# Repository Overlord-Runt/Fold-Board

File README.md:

# Fold Board
Made By Overlord Runt // Taran The Idiot

## The Fold Board
Its the second keyboard in my line of Taranium boards. It is a keyboard that folds! It has 66 Keys and an OLED for funny stuff.

If you like this project, please give it a star!

YouTube vid: https://youtube.com/shorts/LQNGhtRMvZQ?si=ZyAIBXtM6X78Itwt

## CAD

Here is a full [CAD Build](https://cad.onshape.com/documents/464e86edd9a4b3695068071c/w/4e80d06eb9a86776c724470c/e/258c53a4e91dc0ec03e526f0) of the keyboard.\
It uses a rubber band to hold the 2 halves together and I am probably gonna have to work on the joint a bit when i get the parts.

The case is 44cm tall when layed flat out which is pretty good for a folding board. I made sure to keep the joint loose but strong enough to stay on so it doesnt wear down as muhttps://youtube.com/shorts/LQNGhtRMvZQ?si=ZyAIBXtM6X78Itwtch and stays nice. I suggest printing it from petg so you can get more slip.

Here are some shots of what it looks like open and folded.

I spent majority of my time here going through different renditions of the bridge and trying different ways to make the fold work while keeping it as a keyboard that it viable to use.

## PCB

The pcb was done pretty quickly and I only did about 1 revision while making it.\
The pcb folder contains the original design files while right and left side have the files with the respective side isolated for fabrication purposes. gerbers can also be found in those folders.

I used 16 jumper wires to bridge the connections of one half to the other instead of going for the traditional approach with trrs. I think will add a nice look to it, especially across the bridge.

My schematic is pretty normal. Average split board stuff.

## Firmware

This keyboard uses QMK firmware that can be found in the firmware folder. Unfortunately it isnt compiled as my computer is too old to install the QMK command line but I will update it as soon as I can. For now you need to install the command line yourself [here](https://docs.qmk.fm/newbs_getting_started).

This was probably my fastest firmware built ever. Its all thanks to github copilot. It completely gets rid of all the zombie work. I can finally be free. There is no greater blessing to the world.

## BOM
BOM can be found [here](https://github.com/Overlord-Runt/Fold-Board/blob/main/BOM.md) but here is a general list:
- 66 MX Switches
- 66 diodes
- 2 2U stablisers
- 64 1U keycaps
- 2 2U keycaps
- 2 PCBs
- 5 3D printd Case parts
- SSD1306 128x32 OLED
- 16 50mm long wires
- 1 Orpheus Pico(or a normal pico if you dont have one)
- 1 large rubber band
- 8 M3D5L6 Heatsets
- 8 M3 30mm long screws

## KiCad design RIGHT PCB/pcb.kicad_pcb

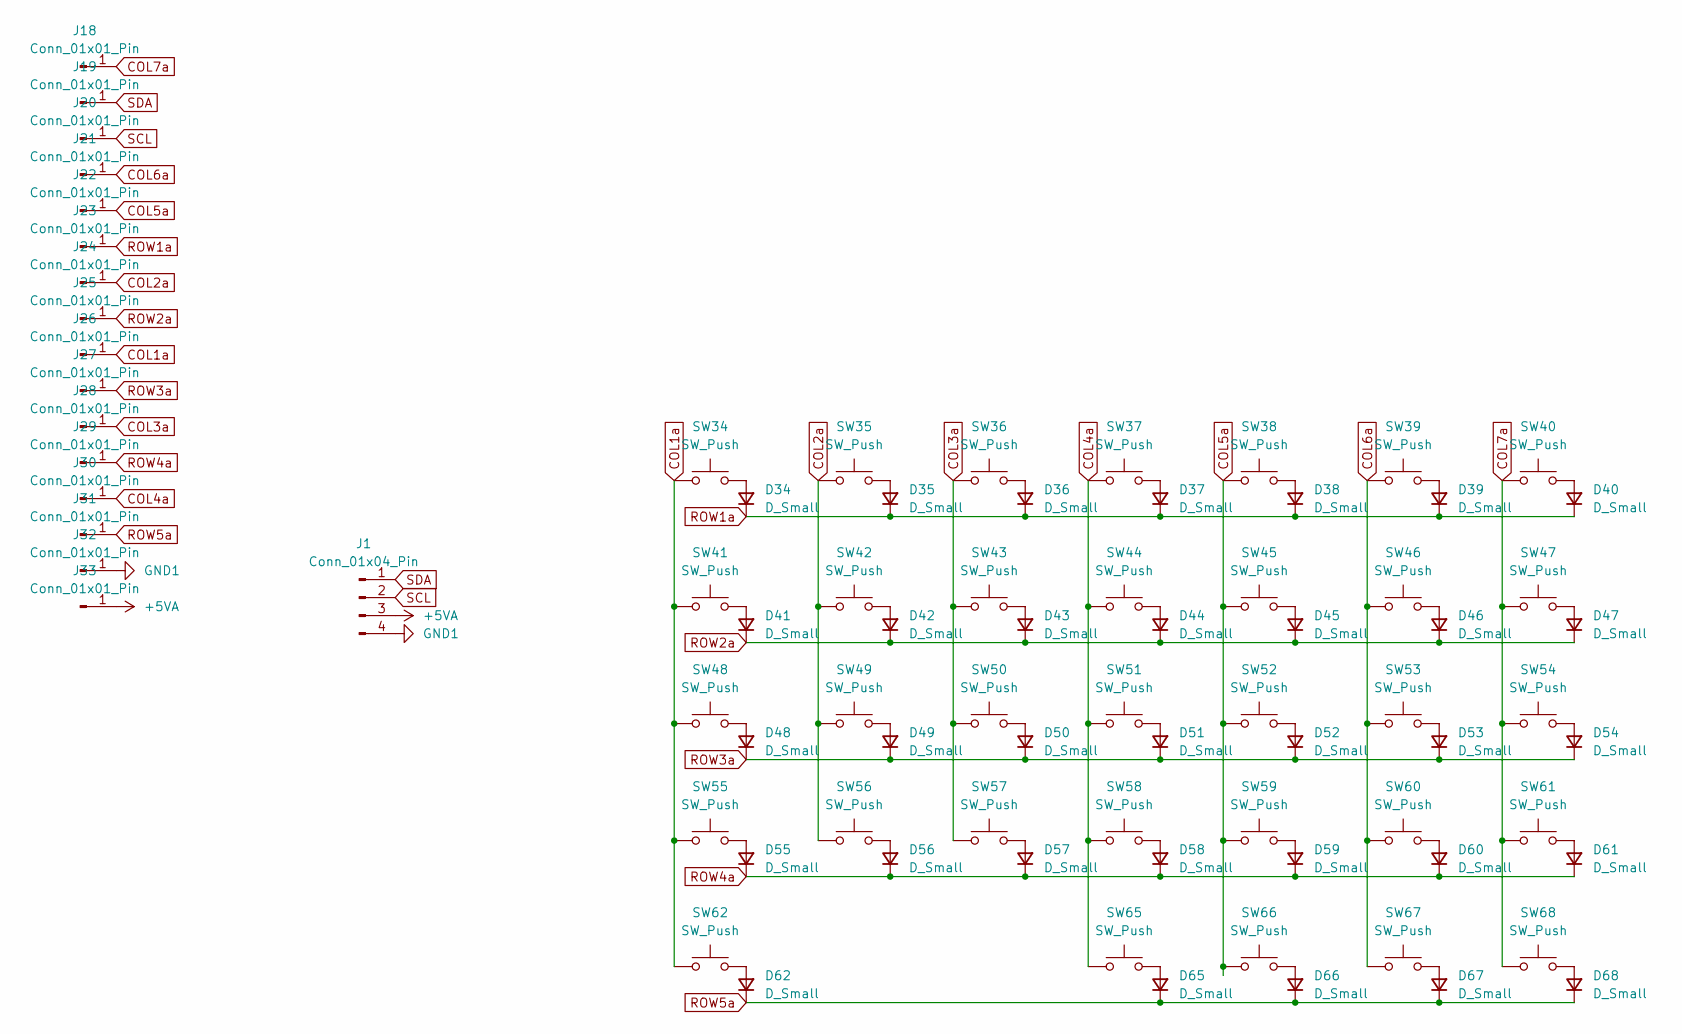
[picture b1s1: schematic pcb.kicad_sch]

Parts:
D34, D35, D36, D37, D38, D39, D40, D41, D42, D43, D44, D45, D46, D47, D48, D49, D50, D51, D52, D53, D54, D55, D56, D57, D58, D59, D60, D61, D62, D65, D66, D67, D68: D_Small; D_DO-35_SOD27_P7.62mm_Horizontal
J1: Conn_01x04_Pin; PinSocket_1x04_P2.54mm_Vertical
J18, J19, J20, J21, J22, J23, J24, J25, J26, J27, J28, J29, J30, J31, J32, J33: Conn_01x01_Pin; TestPoint_Pad_3.0x3.0mm
SW34, SW35, SW36, SW37, SW38, SW39, SW40, SW41, SW42, SW43, SW44, SW45, SW46, SW47, SW48, SW49, SW50, SW51, SW52, SW53, SW54, SW55, SW56, SW57, SW58, SW59, SW60, SW61, SW65, SW66, SW67, SW68: SW_Push; SW_Cherry_MX_1.00u_PCB
SW62: SW_Push; SW_Cherry_MX_2.00u_PCB

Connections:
+5VA: J1.3, J33.1
COL1a: J26.1, SW34.1, SW41.1, SW48.1, SW55.1, SW62.1
COL2a: J24.1, SW35.1, SW42.1, SW49.1, SW56.1
COL3a: J28.1, SW36.1, SW43.1, SW50.1, SW57.1
COL4a: J30.1, SW37.1, SW44.1, SW51.1, SW58.1, SW65.1
COL5a: J22.1, SW38.1, SW45.1, SW52.1, SW59.1, SW66.1
COL6a: J21.1, SW39.1, SW46.1, SW53.1, SW60.1, SW67.1
COL7a: J18.1, SW40.1, SW47.1, SW54.1, SW61.1, SW68.1
GND1: J1.4, J32.1
unnamed: D34.2 (A), SW34.2
unnamed: D35.2 (A), SW35.2
unnamed: D36.2 (A), SW36.2
unnamed: D37.2 (A), SW37.2
unnamed: D38.2 (A), SW38.2
unnamed: D39.2 (A), SW39.2
unnamed: D40.2 (A), SW40.2
unnamed: D41.2 (A), SW41.2
unnamed: D42.2 (A), SW42.2
unnamed: D43.2 (A), SW43.2
unnamed: D44.2 (A), SW44.2
unnamed: D45.2 (A), SW45.2
unnamed: D46.2 (A), SW46.2
unnamed: D47.2 (A), SW47.2
unnamed: D48.2 (A), SW48.2
unnamed: D49.2 (A), SW49.2
unnamed: D50.2 (A), SW50.2
unnamed: D51.2 (A), SW51.2
unnamed: D52.2 (A), SW52.2
unnamed: D53.2 (A), SW53.2
unnamed: D54.2 (A), SW54.2
unnamed: D55.2 (A), SW55.2
unnamed: D56.2 (A), SW56.2
unnamed: D57.2 (A), SW57.2
unnamed: D58.2 (A), SW58.2
unnamed: D59.2 (A), SW59.2
unnamed: D60.2 (A), SW60.2
unnamed: D61.2 (A), SW61.2
unnamed: D62.2 (A), SW62.2
unnamed: D65.2 (A), SW65.2
unnamed: D66.2 (A), SW66.2
unnamed: D67.2 (A), SW67.2
unnamed: D68.2 (A), SW68.2
ROW1a: D34.1 (K), D35.1 (K), D36.1 (K), D37.1 (K), D38.1 (K), D39.1 (K), D40.1 (K), J23.1
ROW2a: D41.1 (K), D42.1 (K), D43.1 (K), D44.1 (K), D45.1 (K), D46.1 (K), D47.1 (K), J25.1
ROW3a: D48.1 (K), D49.1 (K), D50.1 (K), D51.1 (K), D52.1 (K), D53.1 (K), D54.1 (K), J27.1
ROW4a: D55.1 (K), D56.1 (K), D57.1 (K), D58.1 (K), D59.1 (K), D60.1 (K), D61.1 (K), J29.1
ROW5a: D62.1 (K), D65.1 (K), D66.1 (K), D67.1 (K), D68.1 (K), J31.1
SCL: J1.2, J20.1
SDA: J1.1, J19.1

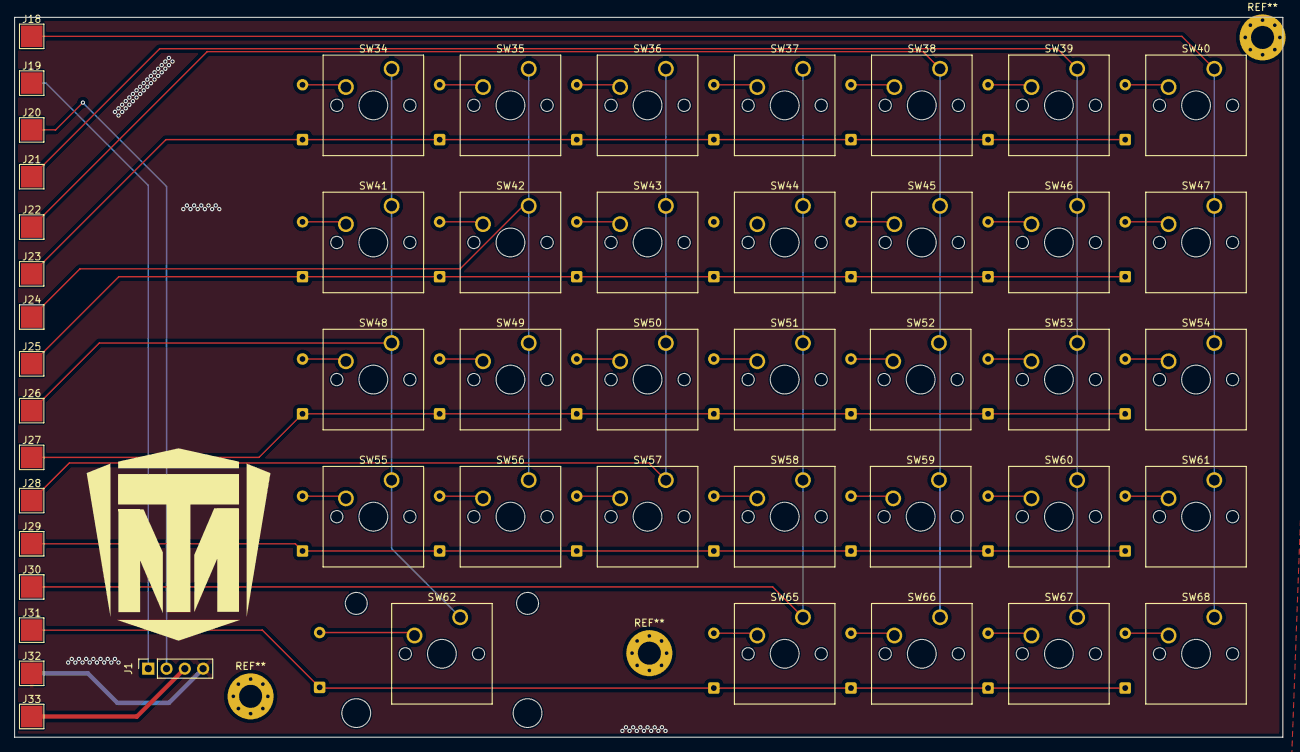
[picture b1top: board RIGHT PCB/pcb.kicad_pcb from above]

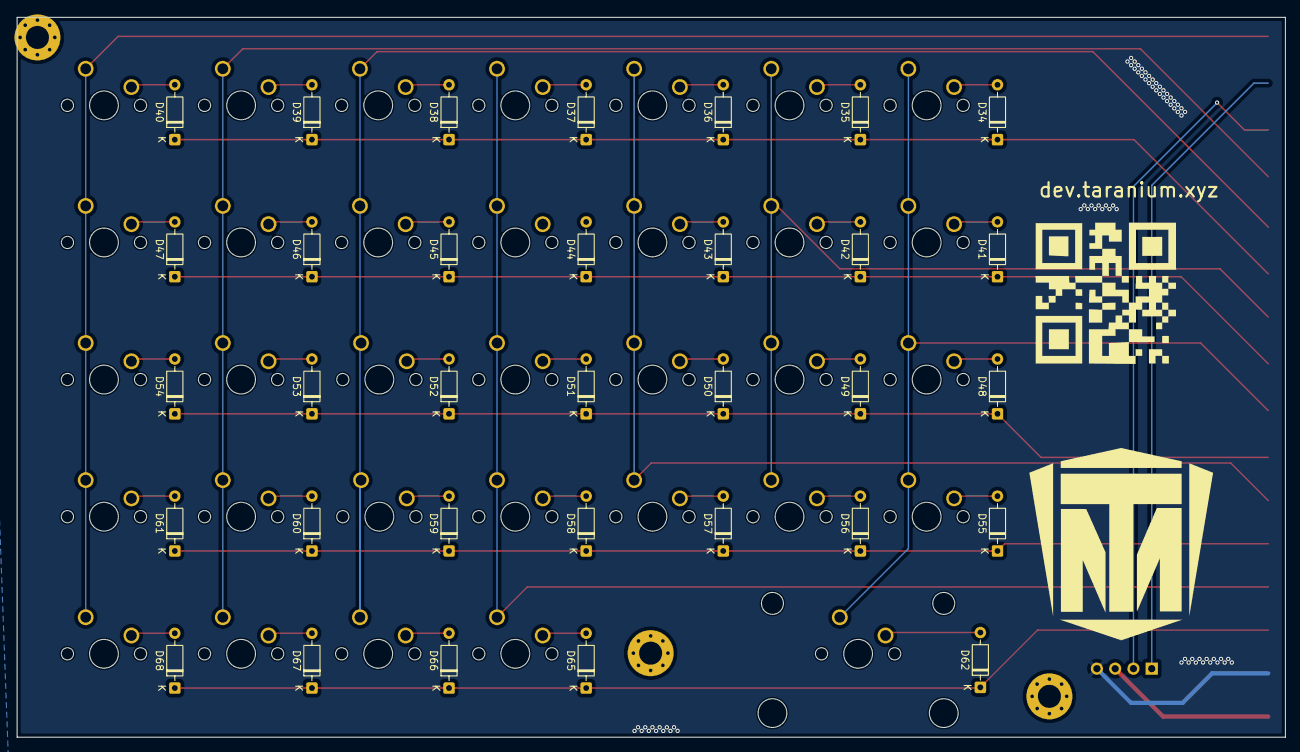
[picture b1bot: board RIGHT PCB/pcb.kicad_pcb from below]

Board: 2 copper layers, 176.2 x 100.0 mm, 83 parts (33 on the bottom side), 49 nets.

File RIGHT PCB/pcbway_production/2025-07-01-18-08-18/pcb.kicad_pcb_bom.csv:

Designator,Quantity,Value,Footprint,Package,MPN,DNP,Mount_Type,Description,Sim.Device,Sim.Pins
"D34, D35, D36, D37, D38, D39, D40, D41, D42, D43, D44, D45, D46, D47, D48, D49, D50, D51, D52, D53, D54, D55, D56, D57, D58, D59, D60, D61, D62, D65, D66, D67, D68",33,D_Small,D_DO-35_SOD27_P7.62mm_Horizontal,,,,tht,"Diode, small symbol",D,1=K 2=A
J1,1,Conn_01x04_Pin,PinSocket_1x04_P2.54mm_Vertical,,,,tht,"Generic connector, single row, 01x04, script generated",,
"J18, J19, J20, J21, J22, J23, J24, J25, J26, J27, J28, J29, J30, J31, J32, J33",16,Conn_01x01_Pin,TestPoint_Pad_3.0x3.0mm,,,,tht,"Generic connector, single row, 01x01, script generated",,
"SW34, SW35, SW36, SW37, SW38, SW39, SW40, SW41, SW42, SW43, SW44, SW45, SW46, SW47, SW48, SW49, SW50, SW51, SW52, SW53, SW54, SW55, SW56, SW57, SW58, SW59, SW60, SW61, SW65, SW66, SW67, SW68",32,SW_Push,SW_Cherry_MX_1.00u_PCB,,,,tht,"Push button switch, generic, two pins",,
SW62,1,SW_Push,SW_Cherry_MX_2.00u_PCB,,,,tht,"Push button switch, generic, two pins",,

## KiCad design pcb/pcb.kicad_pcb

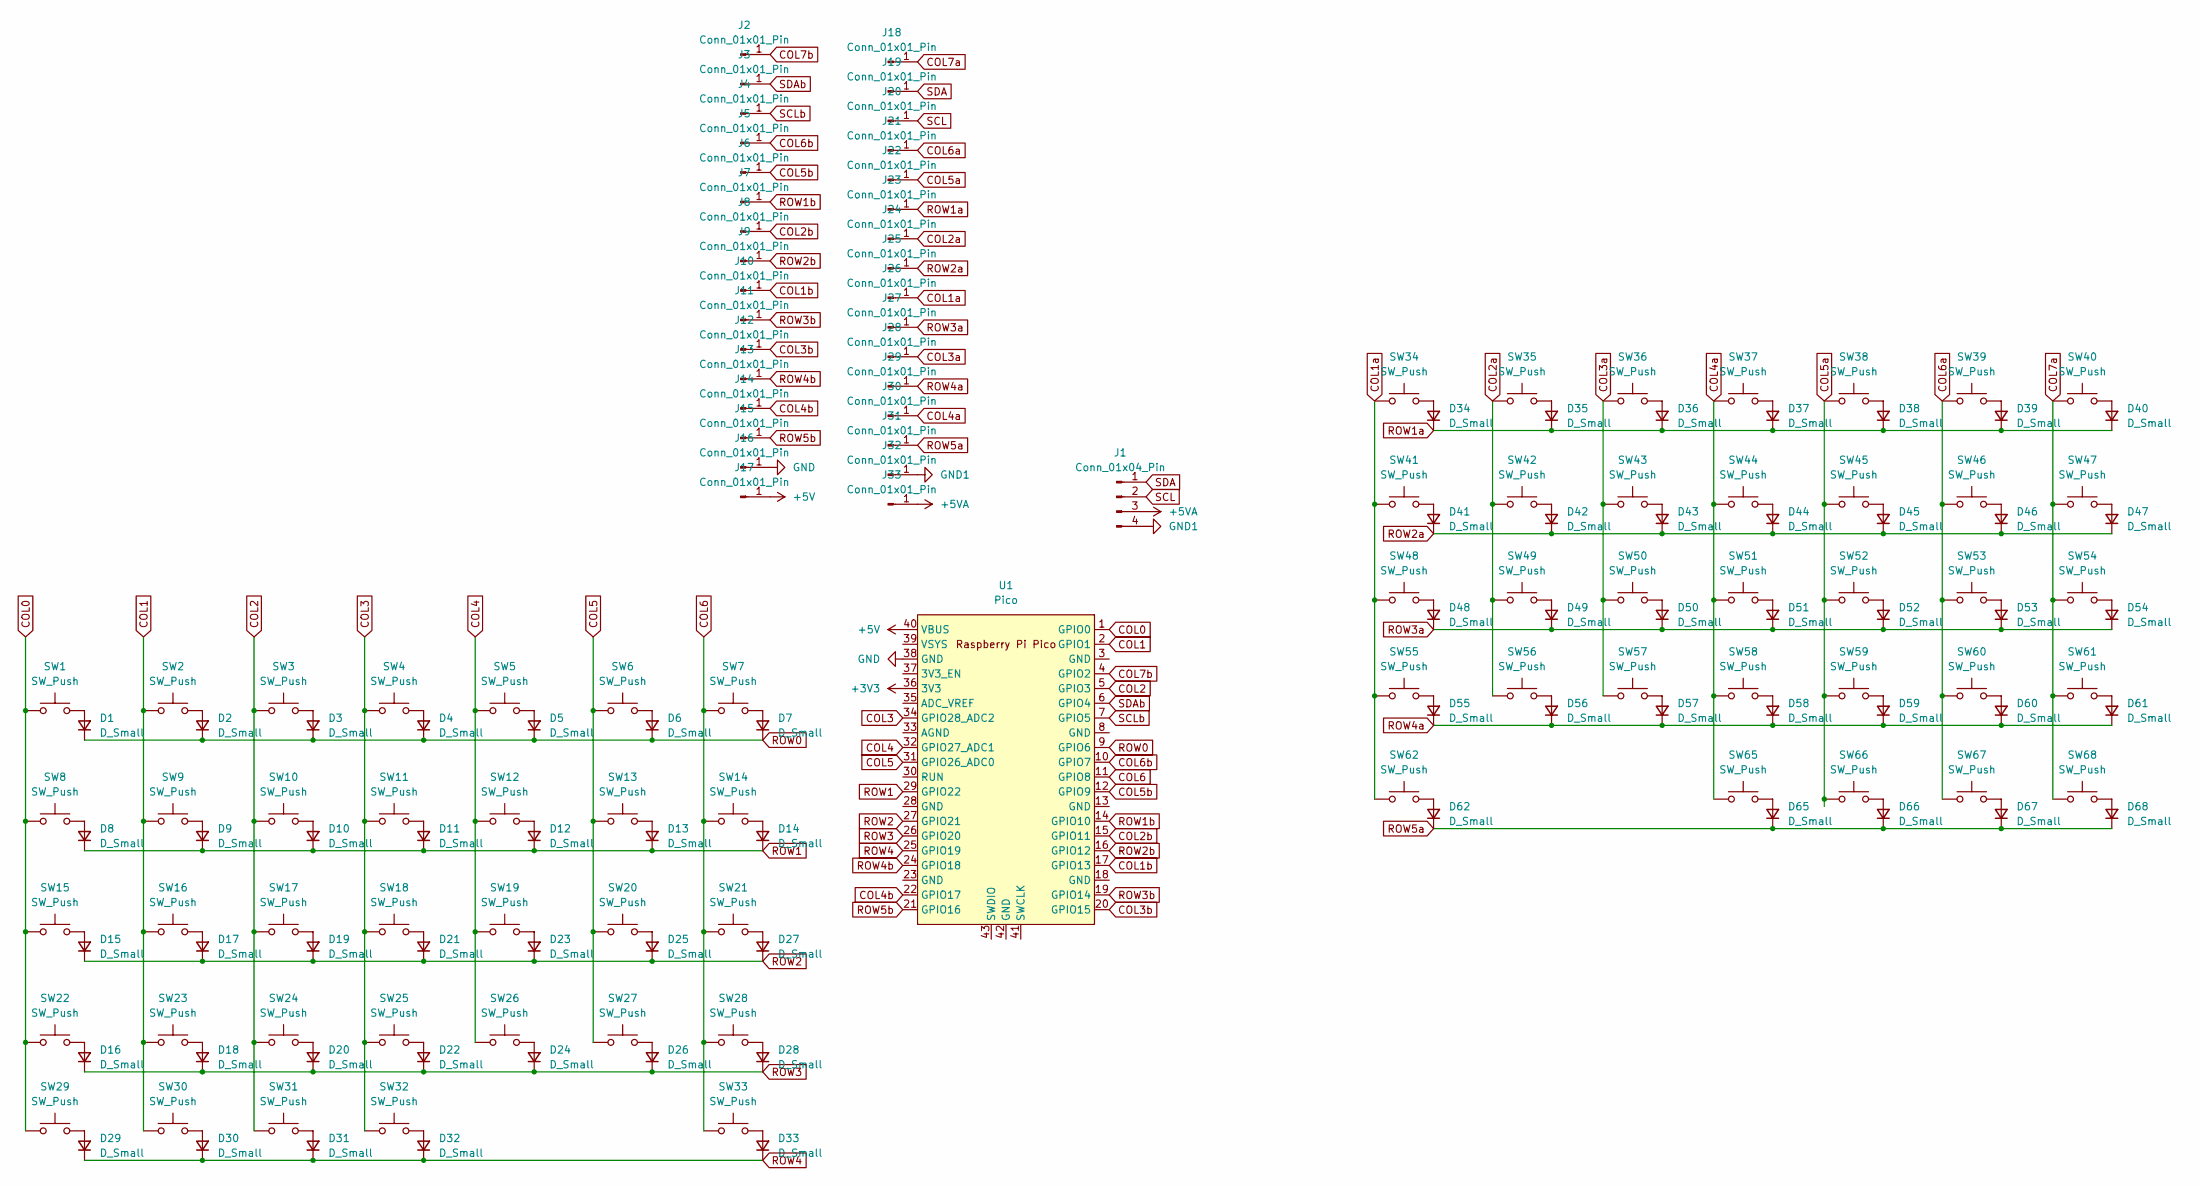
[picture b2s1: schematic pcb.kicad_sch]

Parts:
D1, D2, D3, D4, D5, D6, D7, D8, D9, D10, D11, D12, D13, D14, D15, D16, D17, D18, D19, D20, D21, D22, D23, D24, D25, D26, D27, D28, D29, D30, D31, D32, D33, D34, D35, D36, D37, D38, D39, D40, D41, D42, D43, D44, D45, D46, D47, D48, D49, D50, D51, D52, D53, D54, D55, D56, D57, D58, D59, D60, D61, D62, D65, D66, D67, D68: D_Small; D_DO-35_SOD27_P7.62mm_Horizontal
J1: Conn_01x04_Pin; PinSocket_1x04_P2.54mm_Vertical
J2, J3, J4, J5, J6, J7, J8, J9, J10, J11, J12, J13, J14, J15, J16, J17, J18, J19, J20, J21, J22, J23, J24, J25, J26, J27, J28, J29, J30, J31, J32, J33: Conn_01x01_Pin; TestPoint_Pad_3.0x3.0mm
SW1, SW2, SW3, SW4, SW5, SW6, SW7, SW8, SW9, SW10, SW11, SW12, SW13, SW14, SW15, SW16, SW17, SW18, SW19, SW20, SW21, SW22, SW23, SW24, SW25, SW26, SW27, SW28, SW29, SW30, SW31, SW32, SW34, SW35, SW36, SW37, SW38, SW39, SW40, SW41, SW42, SW43, SW44, SW45, SW46, SW47, SW48, SW49, SW50, SW51, SW52, SW53, SW54, SW55, SW56, SW57, SW58, SW59, SW60, SW61, SW65, SW66, SW67, SW68: SW_Push; SW_Cherry_MX_1.00u_PCB
SW33, SW62: SW_Push; SW_Cherry_MX_2.00u_PCB
U1: Pico; RPi_Pico_SMD_TH

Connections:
+3V3: U1.36 (3V3)
+5V: J17.1, U1.40 (VBUS)
+5VA: J1.3, J33.1
COL0: SW1.1, SW8.1, SW15.1, SW22.1, SW29.1, U1.1 (GPIO0)
COL1: SW2.1, SW9.1, SW16.1, SW23.1, SW30.1, U1.2 (GPIO1)
COL1a: J26.1, SW34.1, SW41.1, SW48.1, SW55.1, SW62.1
COL1b: J10.1, U1.17 (GPIO13)
COL2: SW3.1, SW10.1, SW17.1, SW24.1, SW31.1, U1.5 (GPIO3)
COL2a: J24.1, SW35.1, SW42.1, SW49.1, SW56.1
COL2b: J8.1, U1.15 (GPIO11)
COL3: SW4.1, SW11.1, SW18.1, SW25.1, SW32.1, U1.34 (GPIO28_ADC2)
COL3a: J28.1, SW36.1, SW43.1, SW50.1, SW57.1
COL3b: J12.1, U1.20 (GPIO15)
COL4: SW5.1, SW12.1, SW19.1, SW26.1, U1.32 (GPIO27_ADC1)
COL4a: J30.1, SW37.1, SW44.1, SW51.1, SW58.1, SW65.1
COL4b: J14.1, U1.22 (GPIO17)
COL5: SW6.1, SW13.1, SW20.1, SW27.1, U1.31 (GPIO26_ADC0)
COL5a: J22.1, SW38.1, SW45.1, SW52.1, SW59.1, SW66.1
COL5b: J6.1, U1.12 (GPIO9)
COL6: SW7.1, SW14.1, SW21.1, SW28.1, SW33.1, U1.11 (GPIO8)
COL6a: J21.1, SW39.1, SW46.1, SW53.1, SW60.1, SW67.1
COL6b: J5.1, U1.10 (GPIO7)
COL7a: J18.1, SW40.1, SW47.1, SW54.1, SW61.1, SW68.1
COL7b: J2.1, U1.4 (GPIO2)
GND: J16.1, U1.38 (GND)
GND1: J1.4, J32.1
unnamed: D1.2 (A), SW1.2
unnamed: D2.2 (A), SW2.2
unnamed: D3.2 (A), SW3.2
unnamed: D4.2 (A), SW4.2
unnamed: D5.2 (A), SW5.2
unnamed: D6.2 (A), SW6.2
unnamed: D7.2 (A), SW7.2
unnamed: D8.2 (A), SW8.2
unnamed: D9.2 (A), SW9.2
unnamed: D10.2 (A), SW10.2
unnamed: D11.2 (A), SW11.2
unnamed: D12.2 (A), SW12.2
unnamed: D13.2 (A), SW13.2
unnamed: D14.2 (A), SW14.2
unnamed: D15.2 (A), SW15.2
unnamed: D16.2 (A), SW22.2
unnamed: D17.2 (A), SW16.2
unnamed: D18.2 (A), SW23.2
unnamed: D19.2 (A), SW17.2
unnamed: D20.2 (A), SW24.2
unnamed: D21.2 (A), SW18.2
unnamed: D22.2 (A), SW25.2
unnamed: D23.2 (A), SW19.2
unnamed: D24.2 (A), SW26.2
unnamed: D25.2 (A), SW20.2
unnamed: D26.2 (A), SW27.2
unnamed: D27.2 (A), SW21.2
unnamed: D28.2 (A), SW28.2
unnamed: D29.2 (A), SW29.2
unnamed: D30.2 (A), SW30.2
unnamed: D31.2 (A), SW31.2
unnamed: D32.2 (A), SW32.2
unnamed: D33.2 (A), SW33.2
unnamed: D34.2 (A), SW34.2
unnamed: D35.2 (A), SW35.2
unnamed: D36.2 (A), SW36.2
unnamed: D37.2 (A), SW37.2
unnamed: D38.2 (A), SW38.2
unnamed: D39.2 (A), SW39.2
unnamed: D40.2 (A), SW40.2
unnamed: D41.2 (A), SW41.2
unnamed: D42.2 (A), SW42.2
unnamed: D43.2 (A), SW43.2
unnamed: D44.2 (A), SW44.2
unnamed: D45.2 (A), SW45.2
unnamed: D46.2 (A), SW46.2
unnamed: D47.2 (A), SW47.2
unnamed: D48.2 (A), SW48.2
unnamed: D49.2 (A), SW49.2
unnamed: D50.2 (A), SW50.2
unnamed: D51.2 (A), SW51.2
unnamed: D52.2 (A), SW52.2
unnamed: D53.2 (A), SW53.2
unnamed: D54.2 (A), SW54.2
unnamed: D55.2 (A), SW55.2
unnamed: D56.2 (A), SW56.2
unnamed: D57.2 (A), SW57.2
unnamed: D58.2 (A), SW58.2
unnamed: D59.2 (A), SW59.2
unnamed: D60.2 (A), SW60.2
unnamed: D61.2 (A), SW61.2
unnamed: D62.2 (A), SW62.2
unnamed: D65.2 (A), SW65.2
unnamed: D66.2 (A), SW66.2
unnamed: D67.2 (A), SW67.2
unnamed: D68.2 (A), SW68.2
ROW0: D1.1 (K), D2.1 (K), D3.1 (K), D4.1 (K), D5.1 (K), D6.1 (K), D7.1 (K), U1.9 (GPIO6)
ROW1: D8.1 (K), D9.1 (K), D10.1 (K), D11.1 (K), D12.1 (K), D13.1 (K), D14.1 (K), U1.29 (GPIO22)
ROW1a: D34.1 (K), D35.1 (K), D36.1 (K), D37.1 (K), D38.1 (K), D39.1 (K), D40.1 (K), J23.1
ROW1b: J7.1, U1.14 (GPIO10)
ROW2: D15.1 (K), D17.1 (K), D19.1 (K), D21.1 (K), D23.1 (K), D25.1 (K), D27.1 (K), U1.27 (GPIO21)
ROW2a: D41.1 (K), D42.1 (K), D43.1 (K), D44.1 (K), D45.1 (K), D46.1 (K), D47.1 (K), J25.1
ROW2b: J9.1, U1.16 (GPIO12)
ROW3: D16.1 (K), D18.1 (K), D20.1 (K), D22.1 (K), D24.1 (K), D26.1 (K), D28.1 (K), U1.26 (GPIO20)
ROW3a: D48.1 (K), D49.1 (K), D50.1 (K), D51.1 (K), D52.1 (K), D53.1 (K), D54.1 (K), J27.1
ROW3b: J11.1, U1.19 (GPIO14)
ROW4: D29.1 (K), D30.1 (K), D31.1 (K), D32.1 (K), D33.1 (K), U1.25 (GPIO19)
ROW4a: D55.1 (K), D56.1 (K), D57.1 (K), D58.1 (K), D59.1 (K), D60.1 (K), D61.1 (K), J29.1
ROW4b: J13.1, U1.24 (GPIO18)
ROW5a: D62.1 (K), D65.1 (K), D66.1 (K), D67.1 (K), D68.1 (K), J31.1
ROW5b: J15.1, U1.21 (GPIO16)
SCL: J1.2, J20.1
SCLb: J4.1, U1.7 (GPIO5)
SDA: J1.1, J19.1
SDAb: J3.1, U1.6 (GPIO4)

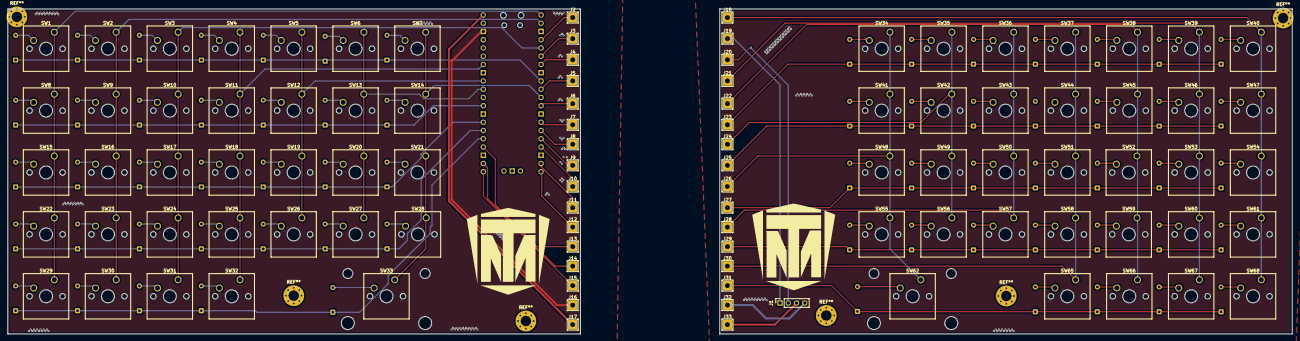
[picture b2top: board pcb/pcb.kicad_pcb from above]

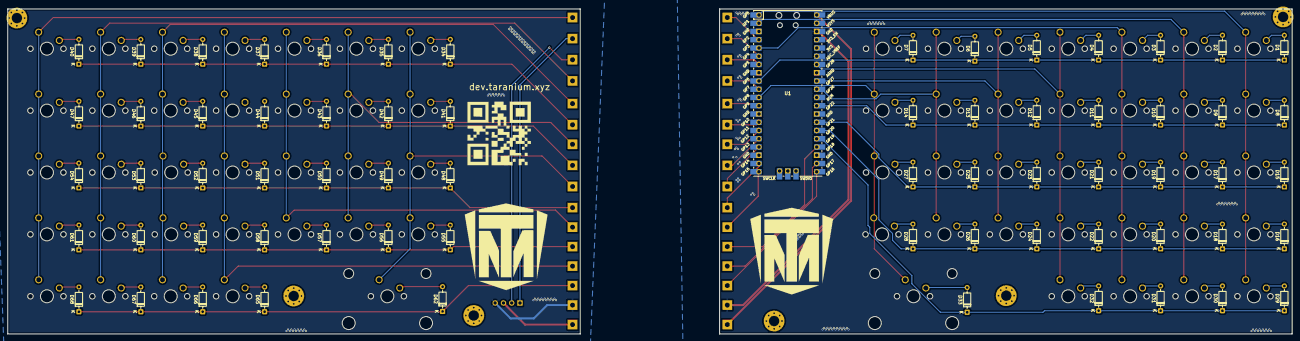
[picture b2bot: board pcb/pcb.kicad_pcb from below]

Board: 2 copper layers, 395.3 x 100.0 mm, 166 parts (67 on the bottom side), 110 nets.

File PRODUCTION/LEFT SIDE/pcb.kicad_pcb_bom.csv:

Designator,Quantity,Value,Footprint,Package,MPN,DNP,Mount_Type,Description,Sim.Device,Sim.Pins
"D1, D10, D11, D12, D13, D14, D15, D16, D17, D18, D19, D2, D20, D21, D22, D23, D24, D25, D26, D27, D28, D29, D3, D30, D31, D32, D33, D4, D5, D6, D7, D8, D9",33,D_Small,D_DO-35_SOD27_P7.62mm_Horizontal,,,,tht,"Diode, small symbol",D,1=K 2=A
"SW1, SW10, SW11, SW12, SW13, SW14, SW15, SW16, SW17, SW18, SW19, SW2, SW20, SW21, SW22, SW23, SW24, SW25, SW26, SW27, SW28, SW29, SW3, SW30, SW31, SW32, SW4, SW5, SW6, SW7, SW8, SW9",32,SW_Push,SW_Cherry_MX_1.00u_PCB,,,,tht,,,
SW33,1,SW_Push,SW_Cherry_MX_2.00u_PCB,,,,tht,"Push button switch, generic, two pins",,
U1,1,Pico,RPi_Pico_SMD_TH,,,,tht,,,

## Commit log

2025-06-12 Create LICENSE
2025-07-01 Rename PRODUCTION/BOM.md to BOM.md
2025-07-02 Create CNAME
